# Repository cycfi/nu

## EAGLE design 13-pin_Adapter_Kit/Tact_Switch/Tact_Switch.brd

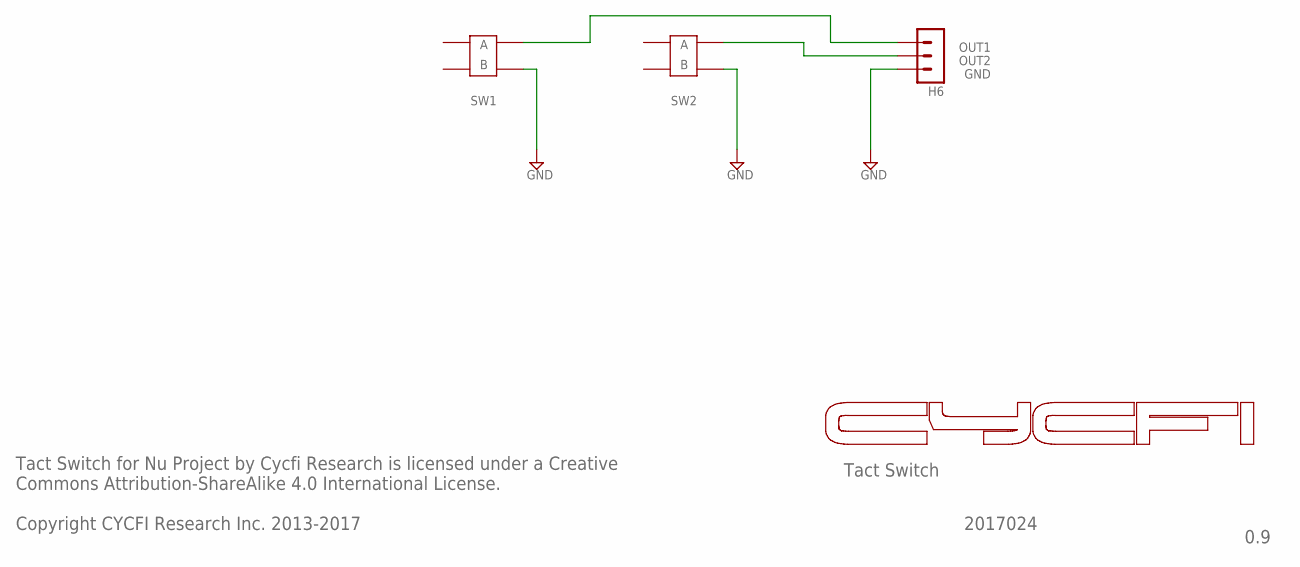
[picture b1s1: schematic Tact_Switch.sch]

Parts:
H6: 3PIN-SMD-2.54MM; 3P-SMD-2.54MM
U$1, U$2: TACT_MJTP1230; MJTP1230

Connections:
GND: H6.P$3 (3), U$1.2B, U$2.2B
unnamed: H6.P$1 (1), U$1.1B
S1: H6.P$2 (2), U$2.1B

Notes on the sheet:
Tact Switch for Nu Project by Cycfi Research is licensed under a Creative Commons Attribution-ShareAlike 4.0 International License. Copyright CYCFI Research Inc. 2013-2017
Tact Switch
OUT1
OUT2
GND
SW1
SW2
2017024
0.9

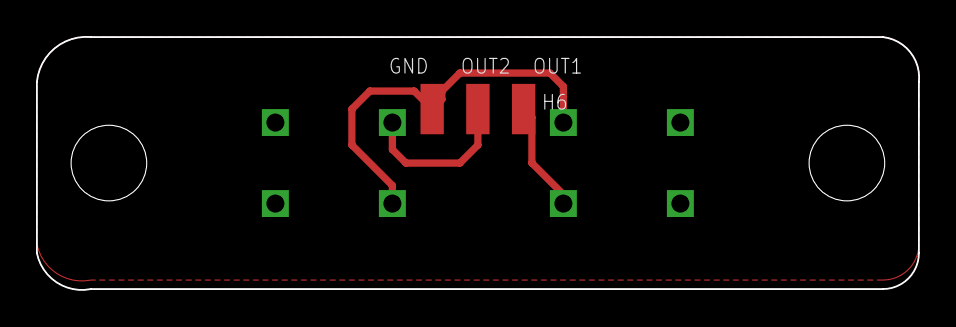
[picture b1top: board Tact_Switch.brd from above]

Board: 2 copper layers, 49.0 x 14.1 mm, 3 parts (0 on the bottom side), 3 nets.

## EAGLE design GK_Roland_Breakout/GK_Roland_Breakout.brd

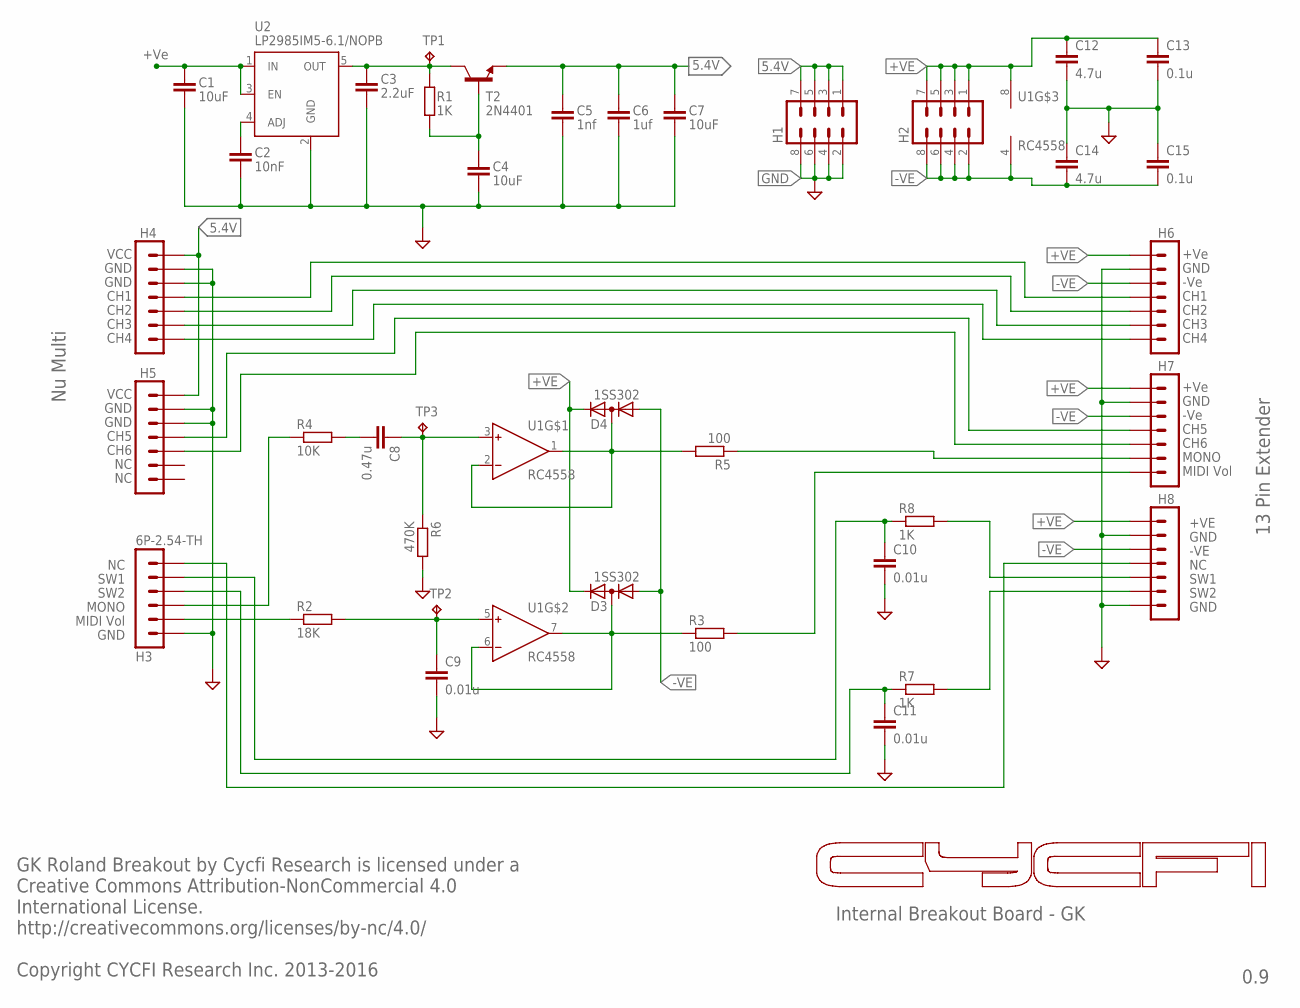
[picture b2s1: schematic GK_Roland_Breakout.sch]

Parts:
C1, C4, C7: 10uF; C0805
C2: 10nF; C0805
C3: 2.2uF; C0805
C5: 1nf; C0603
C6: 1uf; C0603
C8: 0.47u; C0805
C9, C10, C11: 0.01u; C0805
C12, C14: 4.7u; C0805
C13, C15: 0.1u; C0805
D3, D4: 1SS302; SC70-3
H1, H2: MA04-2
H3: 6P-2.54-TH
H4, H5, H6, H7, H8: 7P_ZIF_59453-071110EDHLF
R1, R7, R8: 1K; R0402
R2: 18K; R0402
R3, R5: 100; R0402
R4: 10K; R0402
R6: 470K; R0402
T2: 2N4401; SOT23-3
TP1, TP2, TP3: TPB1,27; B1,27
U1: RC4558; SOIC-8
U2: MIC5205-5V; SOT23-5

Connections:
5.4V: C5.1, C6.1, C7.1, H1.1, H1.3, H1.5, H1.7, H4.P$1 (1), H5.P$1 (1), T2.2 (E)
+VE: C1.1, C12.1, C13.1, D3.2 (K), D4.2 (K), H2.1, H2.3, H2.5, H2.7, H6.P$1 (1), H7.P$1 (1), H8.P$1 (1), U1.8 (V+), U2.1 (IN), U2.3 (EN)
-VE: C14.2, C15.2, D3.1 (A), D4.1 (A), H2.2, H2.4, H2.6, H2.8, H6.P$3 (3), H7.P$3 (3), H8.P$3 (3), U1.4 (V-)
GND: C1.2, C2.2, C3.2, C4.2, C5.2, C6.2, C7.2, C9.2, C10.2, C11.2, C12.2, C13.2, C14.1, C15.1, H1.2, H1.4, H1.6, H1.8, H3.6, H4.P$2 (2), H4.P$3 (3), H5.P$2 (2), H5.P$3 (3), H6.P$2 (2), H7.P$2 (2), H8.P$2 (2), H8.P$7 (7), R6.2, U2.2 (GND)
unnamed: C4.1, R1.2, T2.1 (B)
unnamed: C2.1, U2.4 (ADJ)
unnamed: H4.P$4 (4), H6.P$4 (4)
unnamed: H4.P$5 (5), H6.P$5 (5)
unnamed: H4.P$6 (6), H6.P$6 (6)
unnamed: H4.P$7 (7), H6.P$7 (7)
unnamed: H7.P$6 (6), R5.1
unnamed: H5.P$4 (4), H7.P$4 (4)
unnamed: D3.3 (AK), R3.1, U1.6 (IN-), U1.7 (OUT)
unnamed: C9.1, R2.2, TP2.TP, U1.5 (IN+)
unnamed: H7.P$7 (7), R3.2
unnamed: C8.2, R4.2
unnamed: C8.1, R6.1, TP3.TP, U1.3 (IN+)
unnamed: D4.3 (AK), R5.2, U1.1 (OUT), U1.2 (IN-)
unnamed: H5.P$5 (5), H7.P$5 (5)
unnamed: C10.1, H3.2, R8.1
unnamed: C11.1, H3.3, R7.1
unnamed: H3.4, R4.1
unnamed: H3.5, R2.1
unnamed: H8.P$6 (6), R7.2
unnamed: H8.P$5 (5), R8.2
unnamed: H3.1, H8.P$4 (4)
NC1: C3.1, R1.1, T2.3 (C), TP1.TP, U2.5 (OUT)

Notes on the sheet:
GK Roland Breakout by Cycfi Research is licensed under a Creative Commons Attribution-NonCommercial 4.0 International License. http://creativecommons.org/licenses/by-nc/4.0/ Copyright CYCFI Research Inc. 2013-2016
Internal Breakout Board - GK
LP2985IM5-6.1/NOPB
CH1
CH2
CH3
CH4
CH5
CH6
VCC
GND
+Ve
-Ve
MONO
MIDI Vol
Nu Multi
SW1
SW2
+VE
-VE
13 Pin Extender
0.9

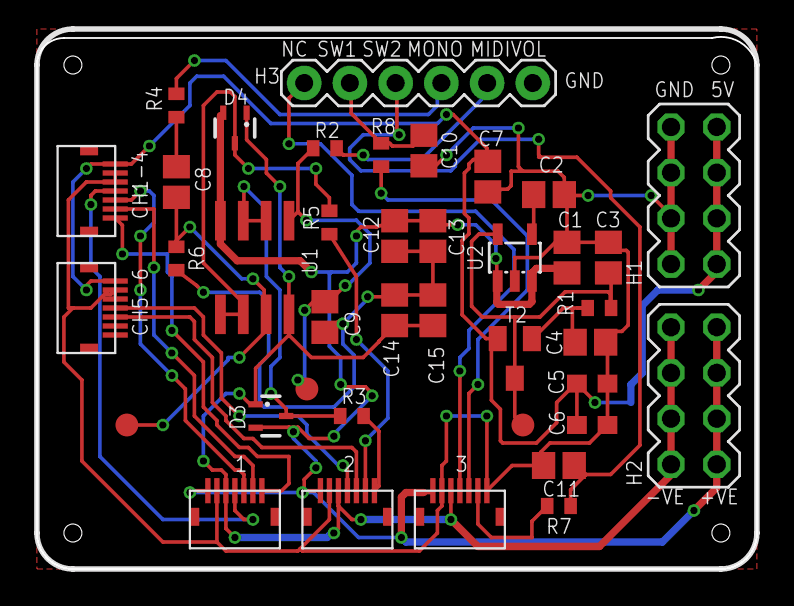
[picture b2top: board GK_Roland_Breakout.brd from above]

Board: 2 copper layers, 40.0 x 29.6 mm, 39 parts (0 on the bottom side), 27 nets.

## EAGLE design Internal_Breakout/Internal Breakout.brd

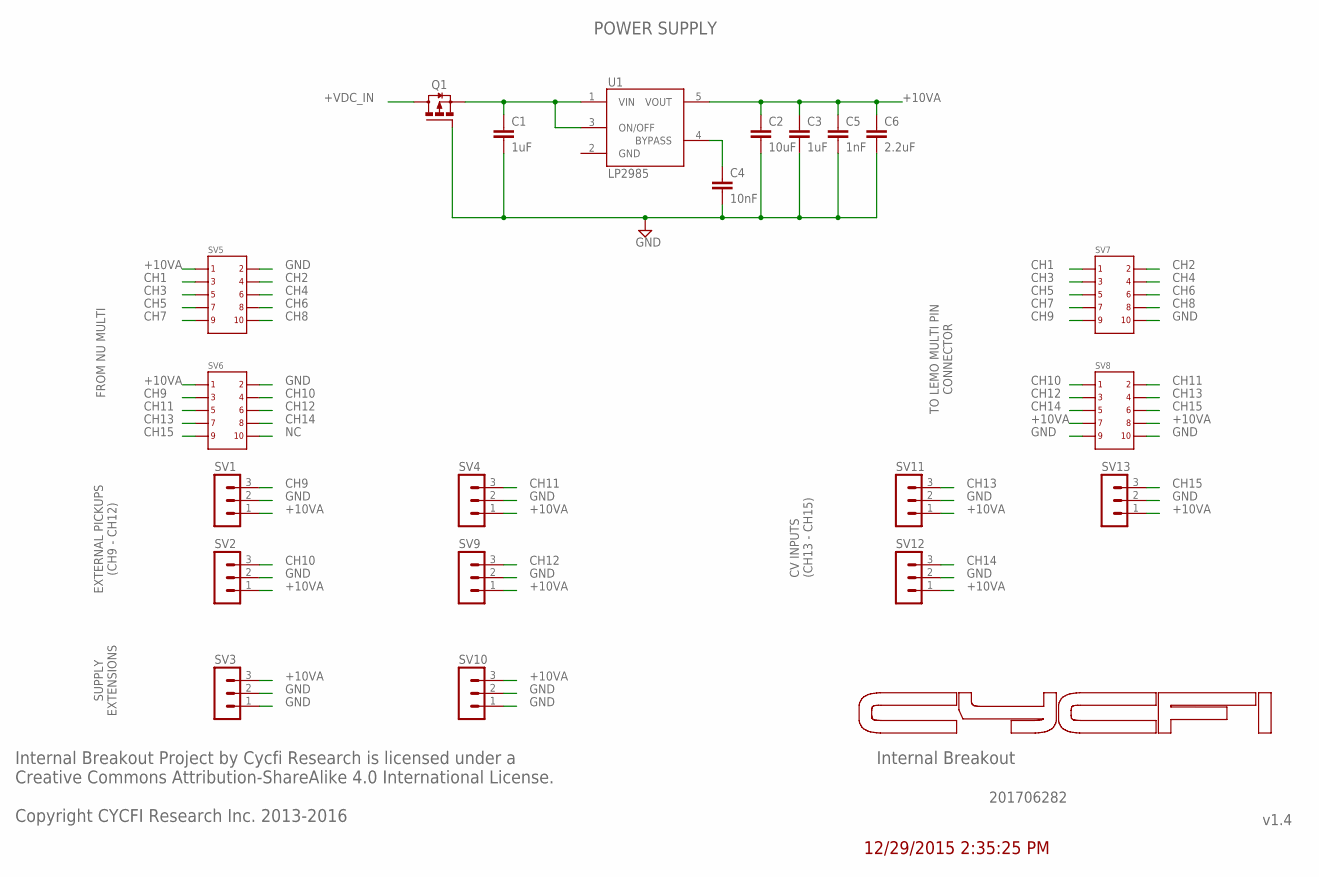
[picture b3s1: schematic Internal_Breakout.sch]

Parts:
C1, C3: 1uF; C0603
C2: 10uF; C0603
C4: 10nF; C0402
C5: 1nF; C0402
C6: 2.2uF; C0603
Q1: FDN360P; SUPER-SOT3
SV1, SV2, SV3, SV4, SV9, SV10, SV11, SV12, SV13: MA03-1
SV5, SV6, SV7, SV8: 2X5
U1: LP2985AIM5-3.3; SOT25

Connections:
+VDC_IN: Q1.3 (D), SV8.7, SV8.8
BYPASS: C4.1, U1.4 (BYPASS)
CH1: SV5.3, SV7.1
CH2: SV5.4, SV7.2
CH3: SV5.5, SV7.3
CH4: SV5.6, SV7.4
CH5: SV5.7, SV7.5
CH6: SV5.8, SV7.6
CH7: SV5.9, SV7.7
CH8: SV5.10, SV7.8
CH9: SV1.3, SV6.3, SV7.9
CH10: SV2.3, SV6.4, SV8.1
CH11: SV4.3, SV6.5, SV8.2
CH12: SV6.6, SV8.3, SV9.3
CH13: SV6.7, SV8.4, SV11.3
CH14: SV6.8, SV8.5, SV12.3
CH15: SV6.9, SV8.6, SV13.3
GND: C1.2, C2.2, C3.2, C4.2, C5.2, C6.2, Q1.1 (G), SV1.2, SV2.2, SV3.1, SV3.2, SV4.2, SV5.2, SV6.2, SV7.10, SV8.9, SV8.10, SV9.2, SV10.1, SV10.2, SV11.2, SV12.2, SV13.2, U1.2 (GND)
unnamed: C1.1, Q1.2 (S), U1.1 (VIN), U1.3 (ON/OFF)
V+: C2.1, C3.1, C5.1, C6.1, SV1.1, SV2.1, SV3.3, SV4.1, SV5.1, SV6.1, SV9.1, SV10.3, SV11.1, SV12.1, SV13.1, U1.5 (VOUT)

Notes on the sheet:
POWER SUPPLY
Internal Breakout
v1.4
Internal Breakout Project by Cycfi Research is licensed under a Creative Commons Attribution-ShareAlike 4.0 International License. Copyright CYCFI Research Inc. 2013-2016
201706282
12/29/2015 2:35:25 PM
+10VA
CH1
CH3
CH5
CH7
GND
CH2
CH4
CH6
CH8
FROM NU MULTI
EXTERNAL PICKUPS (CH9 - CH12)
SUPPLY EXTENSIONS
CV INPUTS (CH13 - CH15)
TO LEMO MULTI PIN CONNECTOR

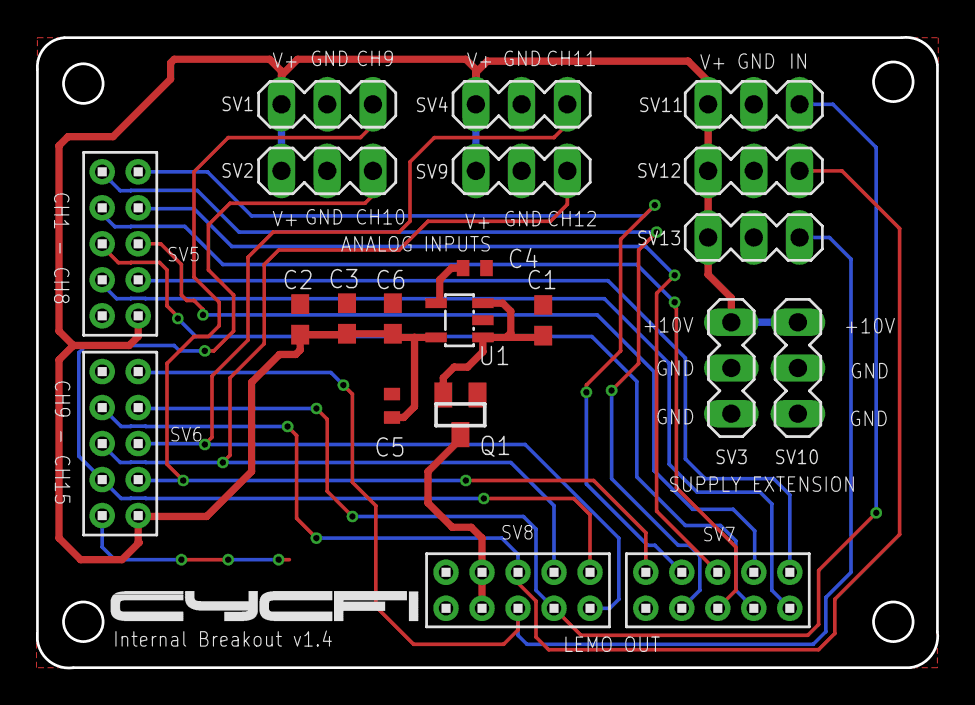
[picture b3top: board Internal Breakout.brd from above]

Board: 2 copper layers, 50.0 x 35.0 mm, 21 parts (0 on the bottom side), 20 nets.

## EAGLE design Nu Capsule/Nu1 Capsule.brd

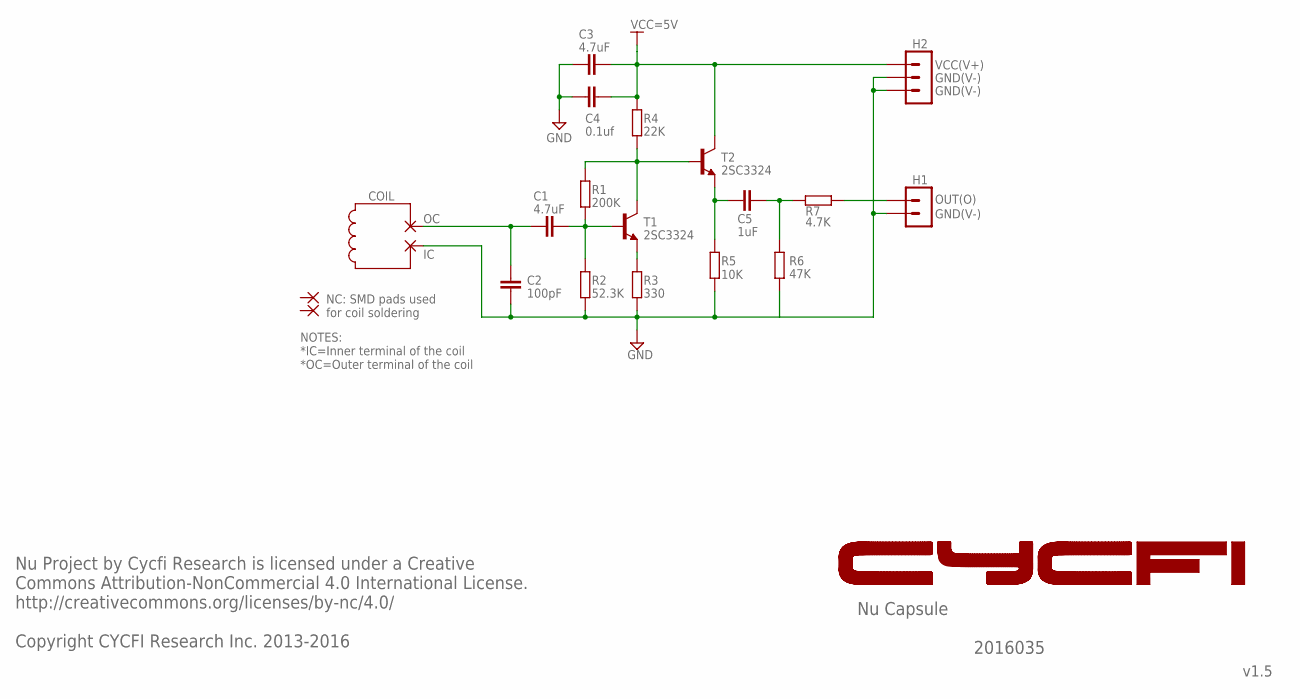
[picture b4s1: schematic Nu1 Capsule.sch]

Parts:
C1: 4.7uF; C0805
C2: 100pF; C0603
C3: 4.7uF; C0603
C4: 0.1uf; C0603
C5: 1uF; C0805
H1: 2P-2MM-TH-MALE; 2P-2MM-TH
H2: 3P-2MM-TH-MALE; 3P-2MM-TH
PAD6, PAD7, PAD18, PAD19: WIREPADSMD1,27-254; SMD1,27-2,54
R1: 200K; R0603
R2: 52.3K; R0805
R3: 330; R0402
R4: 22K; R0402
R5: 10K; R0402
R6: 47K; R0402
R7: 4.7K; R0402
T1, T2: 2SC3324; SOT23

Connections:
GND: C2.1, C3.1, C4.1, H1.P$2 (2), H2.P$2 (2), H2.P$3 (3), PAD7.1, R2.1, R3.1, R5.1, R6.1
unnamed: C1.2, R1.1, R2.2, T1.1 (B)
unnamed: C1.1, C2.2, PAD6.1
unnamed: C5.2, R5.2, T2.2 (E)
unnamed: R3.2, T1.2 (E)
OUT: C5.1, R6.2, R7.1
OUTPUT: H1.P$1 (1), R7.2
VCVF: R1.2, R4.1, T1.3 (C), T2.1 (B)
VIN: C3.2, C4.2, H2.P$1 (1), R4.2, T2.3 (C)

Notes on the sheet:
GND(V-)
OUT(O)
Nu Capsule
v1.5
Nu Project by Cycfi Research is licensed under a Creative Commons Attribution-NonCommercial 4.0 International License. http://creativecommons.org/licenses/by-nc/4.0/ Copyright CYCFI Research Inc. 2013-2016
NC: SMD pads used for coil soldering
VCC(V+)
2016035
COIL
VCC=5V
NOTES: *IC=Inner terminal of the coil *OC=Outer terminal of the coil

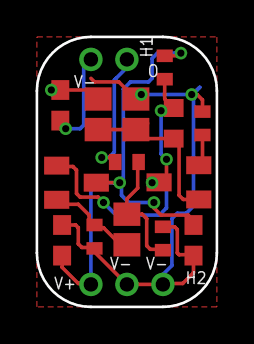
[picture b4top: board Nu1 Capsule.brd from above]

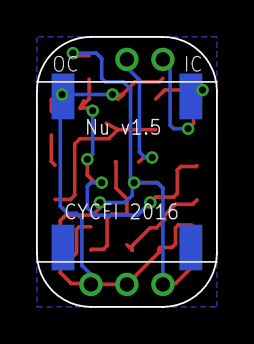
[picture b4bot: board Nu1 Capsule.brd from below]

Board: 2 copper layers, 10.0 x 15.0 mm, 20 parts (4 on the bottom side), 9 nets.

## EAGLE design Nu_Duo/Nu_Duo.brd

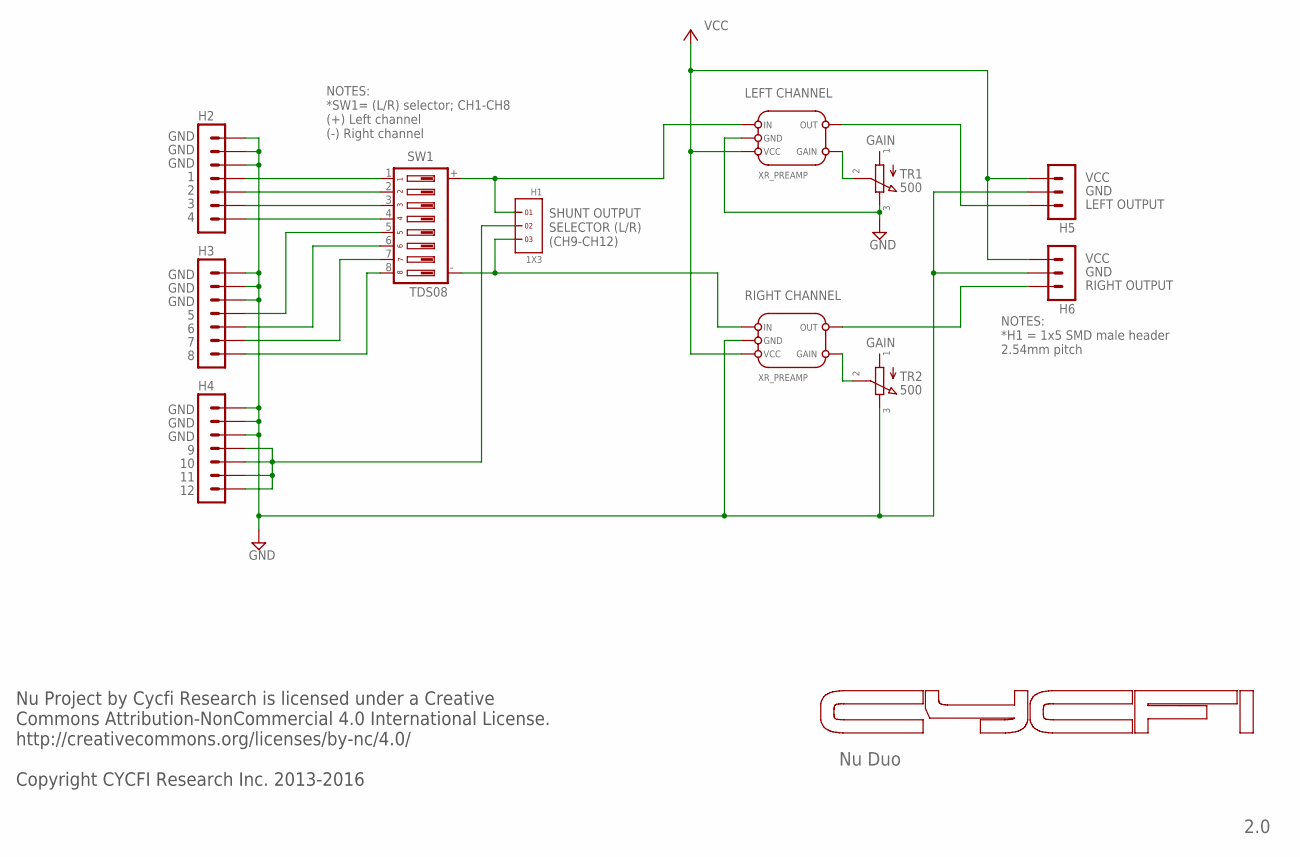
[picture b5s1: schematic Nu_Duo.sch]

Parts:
H1: 1X3
H2, H3, H4: 7P_ZIF_59453-071110EDHLF
H5, H6: 3PIN-SMD-2.54MM; 3P-SMD-2.54MM
P1, P2: XR_PREAMP; XR_PREAMP_V1.5
SW1: TDS08; SPDT-08
TR1, TR2: 500; TC33X-2-201E

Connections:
GND: H2.P$5 (5), H2.P$6 (6), H2.P$7 (7), H3.P$5 (5), H3.P$6 (6), H3.P$7 (7), H4.P$5 (5), H4.P$6 (6), H4.P$7 (7), H5.P$2 (2), H6.P$2 (2), P1.GND, P2.GND, TR1.P$3 (3), TR2.P$3 (3)
LO: H6.P$3 (3), P2.OUT
unnamed: P1.GAIN, TR1.P$2 (2)
unnamed: P2.GAIN, TR2.P$2 (2)
unnamed: H1.2, H4.P$1 (1), H4.P$2 (2), H4.P$3 (3), H4.P$4 (4)
unnamed: H1.1, P1.IN, SW1.+
unnamed: H1.3, P2.IN, SW1.-
unnamed: H2.P$4 (4), SW1.1
unnamed: H2.P$3 (3), SW1.2
unnamed: H2.P$2 (2), SW1.3
unnamed: H2.P$1 (1), SW1.4
unnamed: H3.P$4 (4), SW1.5
unnamed: H3.P$3 (3), SW1.6
unnamed: H3.P$2 (2), SW1.7
unnamed: H3.P$1 (1), SW1.8
RO: H5.P$3 (3), P1.OUT
VCC: H5.P$1 (1), H6.P$1 (1), P1.VCC, P2.VCC

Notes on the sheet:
Nu Duo
GND
LEFT CHANNEL
RIGHT CHANNEL
SHUNT OUTPUT SELECTOR (L/R) (CH9-CH12)
GAIN
NOTES: *SW1= (L/R) selector; CH1-CH8 (+) Left channel (-) Right channel
NOTES: *H1 = 1x5 SMD male header 2.54mm pitch
VCC
RIGHT OUTPUT
LEFT OUTPUT
2.0
Nu Project by Cycfi Research is licensed under a Creative Commons Attribution-NonCommercial 4.0 International License. http://creativecommons.org/licenses/by-nc/4.0/ Copyright CYCFI Research Inc. 2013-2016

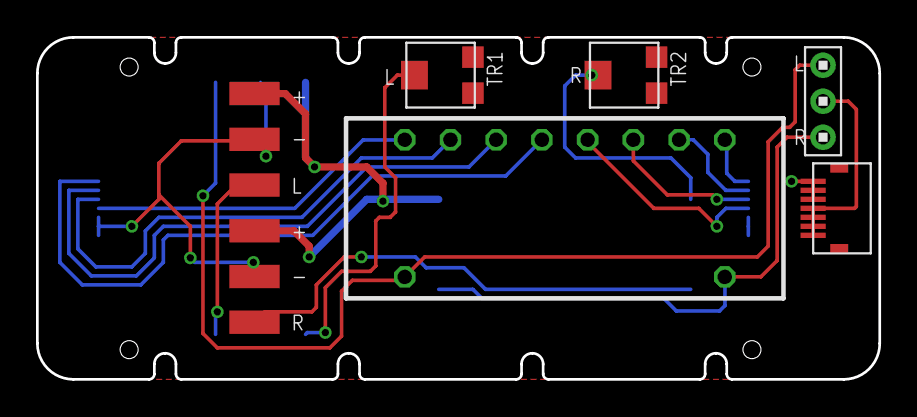
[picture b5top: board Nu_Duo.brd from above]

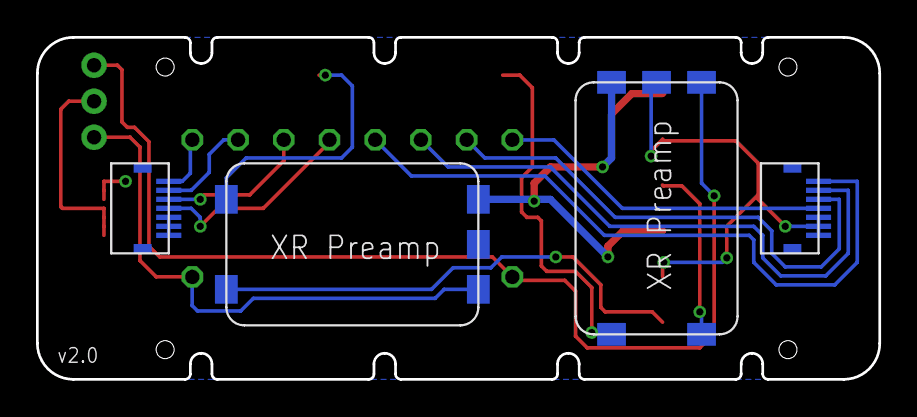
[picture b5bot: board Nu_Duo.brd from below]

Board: 2 copper layers, 46.8 x 19.0 mm, 11 parts (4 on the bottom side), 17 nets.

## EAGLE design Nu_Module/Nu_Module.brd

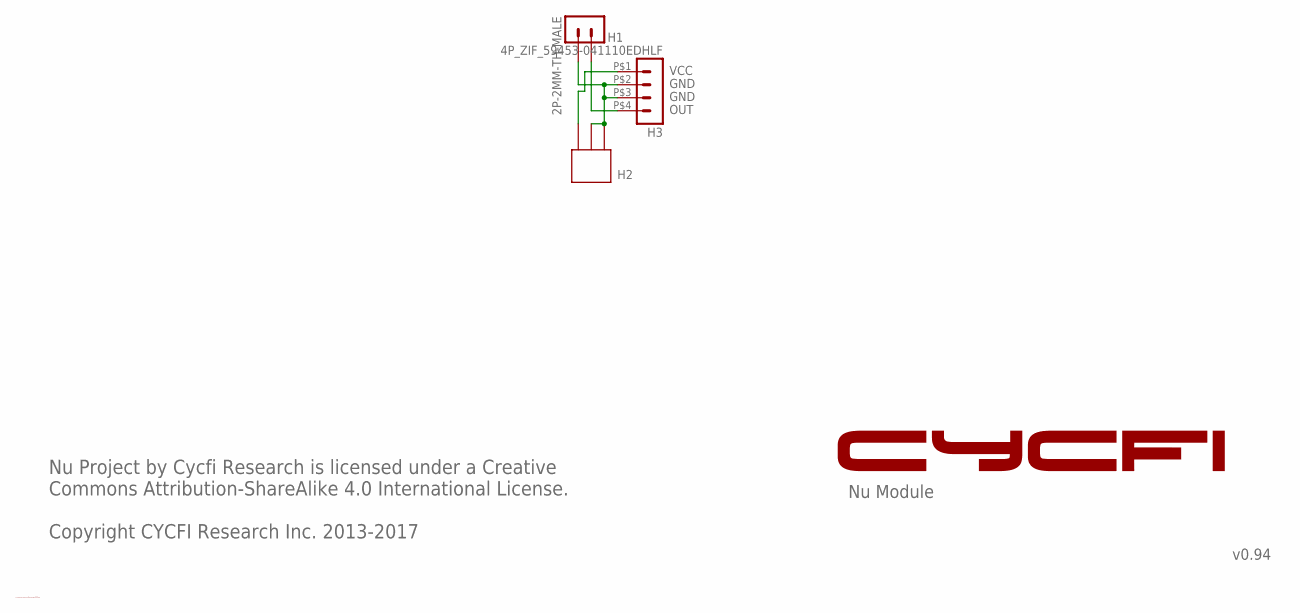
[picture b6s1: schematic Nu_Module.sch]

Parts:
H1: 2P-2MM-TH-MALE; 2P-2MM-TH
H2: 951102-8622-AR; 3P-TH-2MM
H3: 4P_ZIF_59453-041110EDHLF

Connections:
GND: H1.P$1 (1), H2.P$1, H2.P$2, H3.P$2 (2), H3.P$3 (3)
unnamed: H1.P$2 (2), H3.P$4 (4)
unnamed: H2.P$3, H3.P$1 (1)

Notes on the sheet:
GND
OUT
VCC
Nu Module
v0.94
Nu Project by Cycfi Research is licensed under a Creative Commons Attribution-ShareAlike 4.0 International License. Copyright CYCFI Research Inc. 2013-2017
C:/Users/mark belarmino/Desktop/Logo-2016.bmp

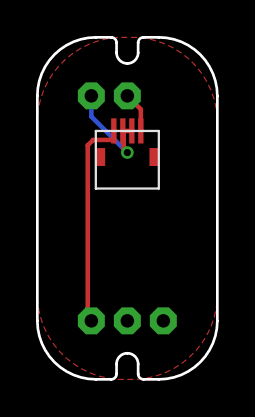
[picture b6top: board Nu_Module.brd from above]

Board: 2 copper layers, 10.0 x 19.0 mm, 3 parts (0 on the bottom side), 3 nets.

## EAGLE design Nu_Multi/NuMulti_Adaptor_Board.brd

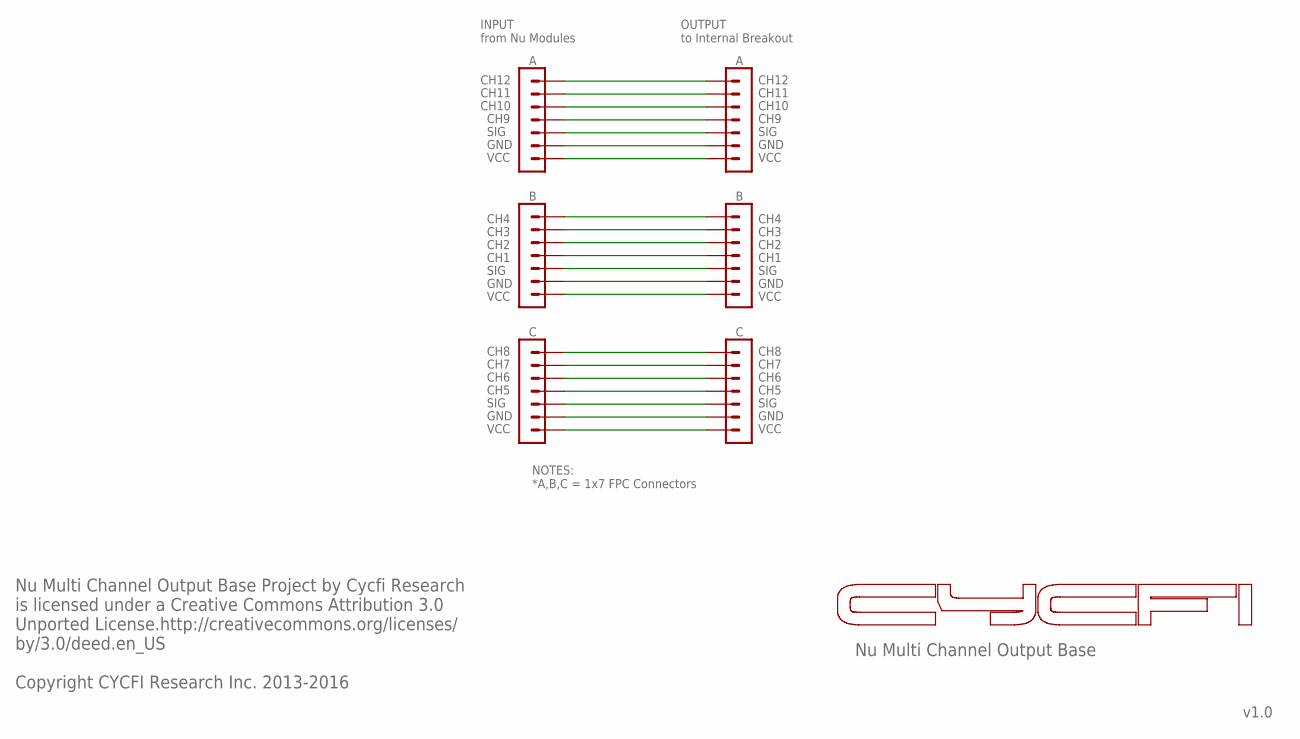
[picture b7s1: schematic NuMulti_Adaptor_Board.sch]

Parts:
H1, H2, H3, H4, H5, H6: 7P_ZIF_59453-071110EDHLF

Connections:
GND: H1.P$6 (6), H2.P$6 (6), H3.P$6 (6), H4.P$6 (6), H5.P$6 (6), H6.P$6 (6)
unnamed: H5.P$1 (1), H6.P$1 (1)
unnamed: H5.P$2 (2), H6.P$2 (2)
unnamed: H5.P$3 (3), H6.P$3 (3)
unnamed: H5.P$4 (4), H6.P$4 (4)
unnamed: H5.P$5 (5), H6.P$5 (5)
unnamed: H5.P$7 (7), H6.P$7 (7)
unnamed: H2.P$7 (7), H4.P$7 (7)
unnamed: H2.P$5 (5), H4.P$5 (5)
unnamed: H2.P$4 (4), H4.P$4 (4)
unnamed: H2.P$3 (3), H4.P$3 (3)
unnamed: H2.P$2 (2), H4.P$2 (2)
unnamed: H2.P$1 (1), H4.P$1 (1)
unnamed: H1.P$7 (7), H3.P$7 (7)
unnamed: H1.P$5 (5), H3.P$5 (5)
unnamed: H1.P$4 (4), H3.P$4 (4)
unnamed: H1.P$3 (3), H3.P$3 (3)
unnamed: H1.P$2 (2), H3.P$2 (2)
unnamed: H1.P$1 (1), H3.P$1 (1)

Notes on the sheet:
CH4
CH3
CH2
CH1
SIG
GND
VCC
CH8
CH7
CH6
CH5
CH12
CH11
CH10
CH9
Nu Multi Channel Output Base
v1.0
Nu Multi Channel Output Base Project by Cycfi Research is licensed under a Creative Commons Attribution 3.0 Unported License.http://creativecommons.org/licenses/ by/3.0/deed.en_US Copyright CYCFI Research Inc. 2013-2016
INPUT from Nu Modules
OUTPUT to Internal Breakout
NOTES: *A,B,C = 1x7 FPC Connectors

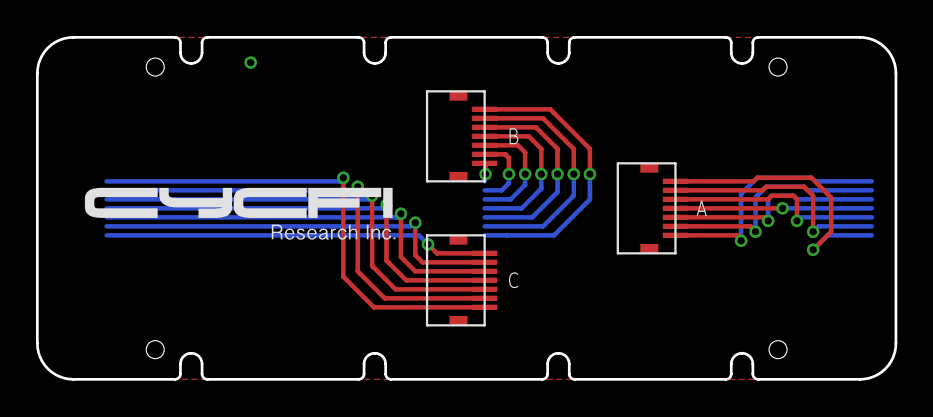
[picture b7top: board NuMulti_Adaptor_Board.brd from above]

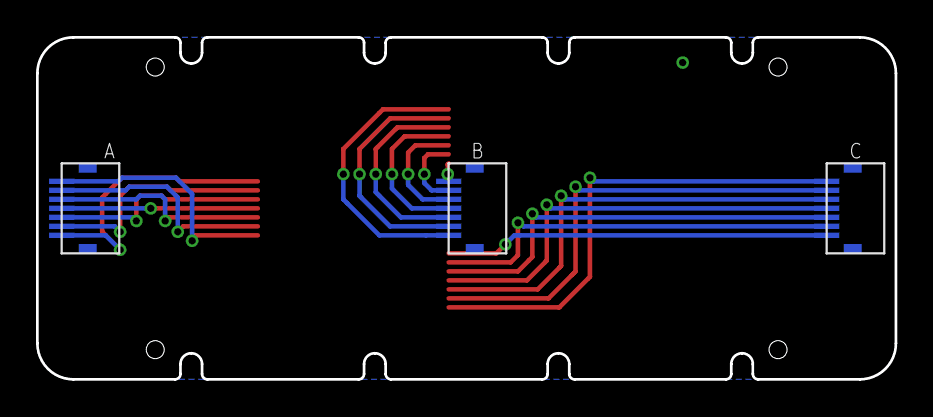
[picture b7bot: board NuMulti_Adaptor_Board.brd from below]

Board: 2 copper layers, 47.7 x 19.0 mm, 6 parts (3 on the bottom side), 19 nets.

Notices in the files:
13-pin_Adapter_Kit/GK_Roland_Breakout/GK_Roland_Breakout.sch:
GK Roland Breakout for Nu Project by Cycfi Research is licensed under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
